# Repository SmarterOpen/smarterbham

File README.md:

# SmarterBham
The SmarterBham project
Imagine a city driven by information.  A place where decision making is supported by a city-wide sensor network that provides real time data about the state of things.  Imagine the platform that runs the network, built and owned by the citizens, measuring the things that we think are important and giving us the insights we need to make our city the best it can be. The SmarterBham project was born out of a recognition that smart cities need grassroots participation. We can combine open hardware designs with open networks, open platforms and open data policies to build a participatory smart cities future.

# Project Structure
* /lopy4 - all the code that runs on the device
* /doc - our documentation.  Requirements, wireframes, flow, security audits, etc
* /web - the web application that we use to manage devices, users, and to analyze collected data

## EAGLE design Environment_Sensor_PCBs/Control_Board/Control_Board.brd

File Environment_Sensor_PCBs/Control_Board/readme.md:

This folder will house the Control Board design filse

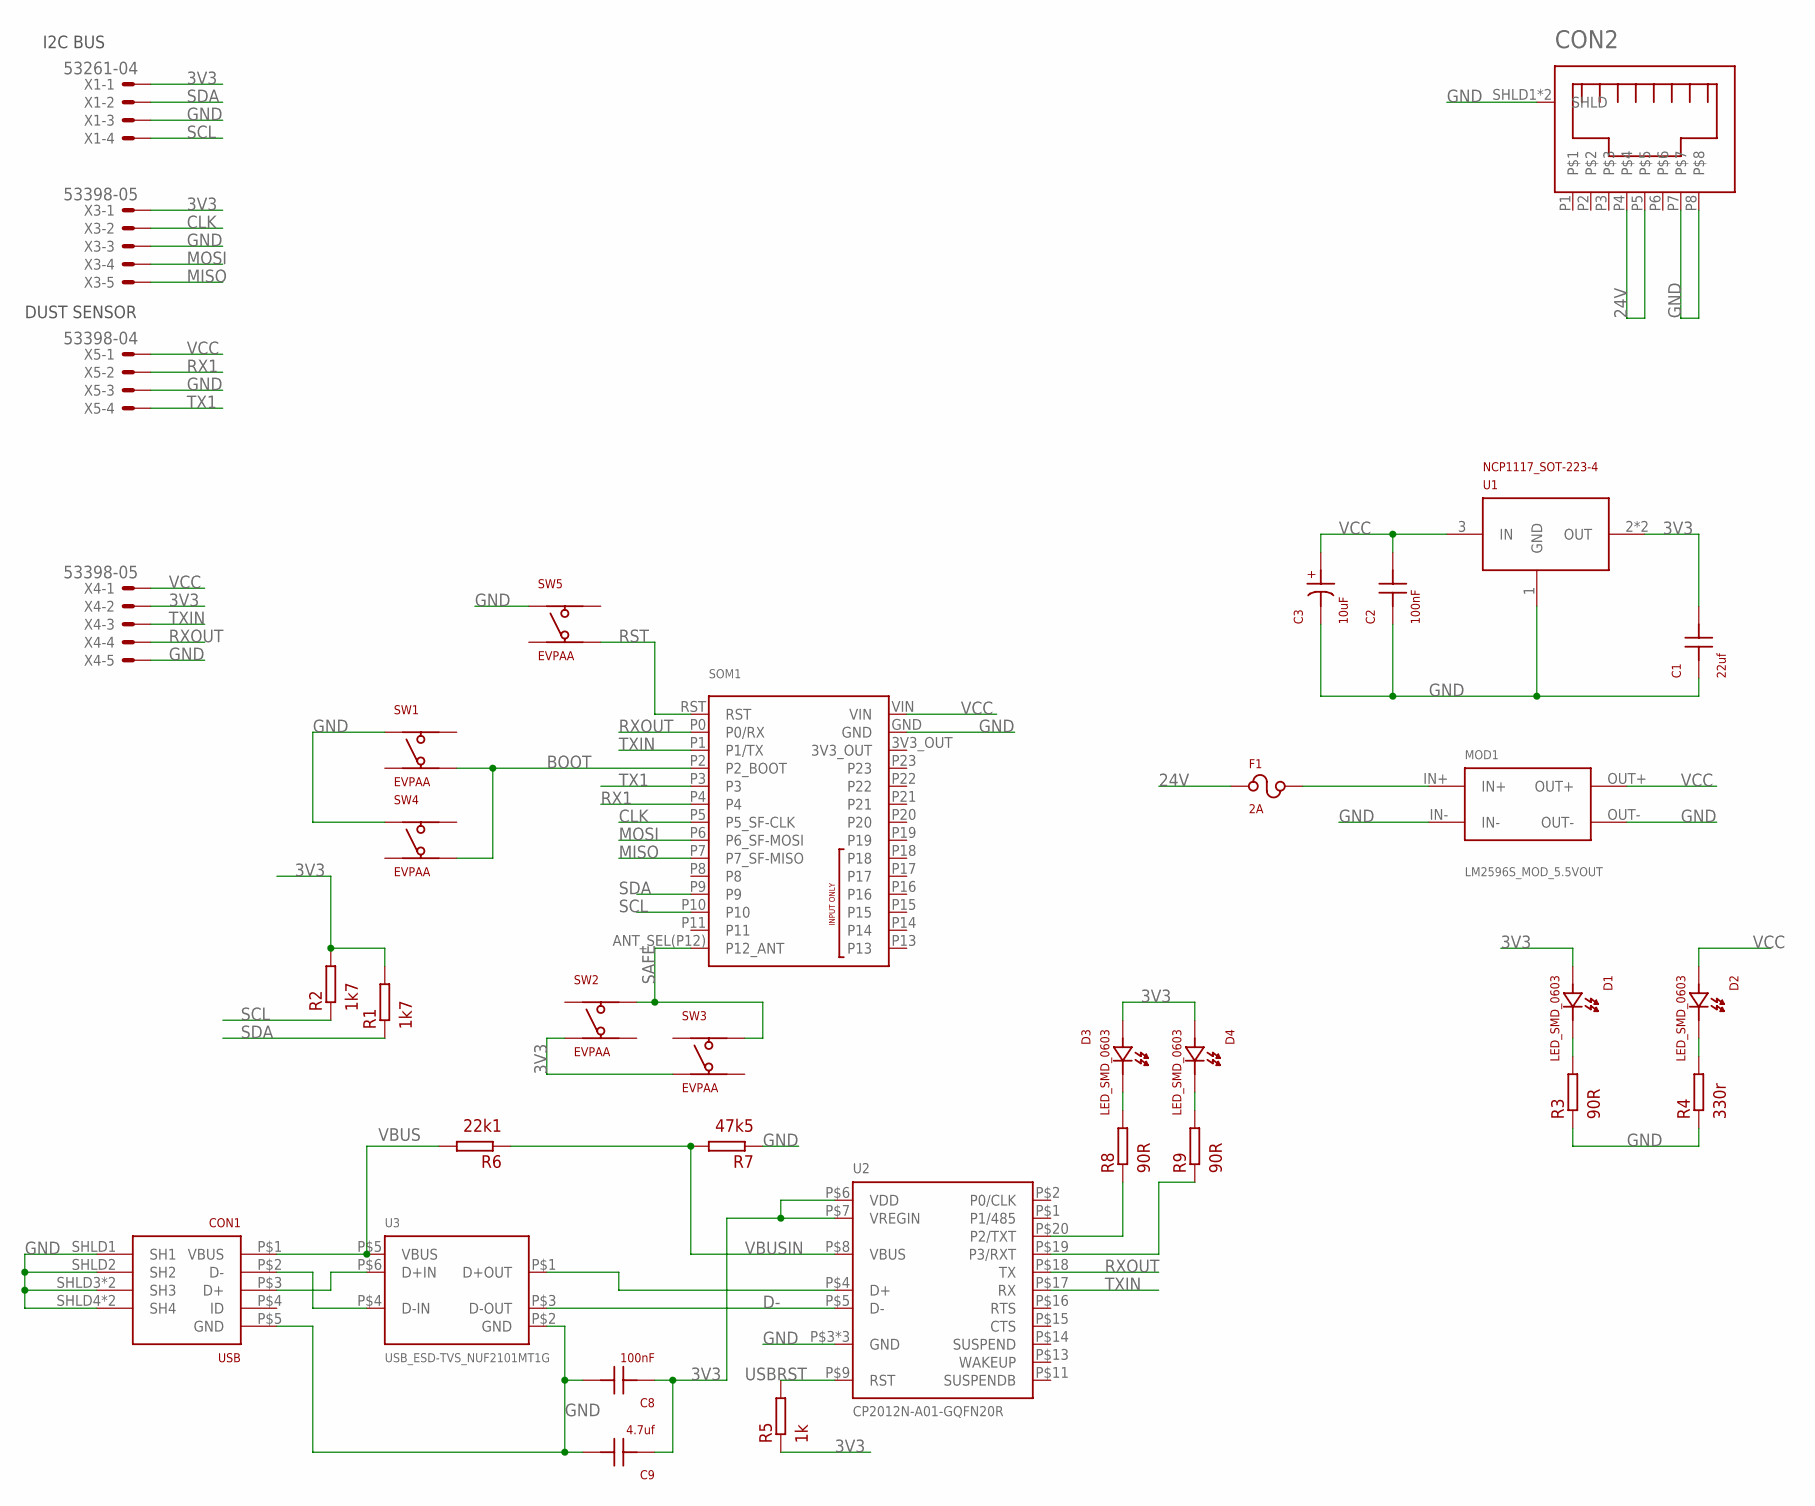
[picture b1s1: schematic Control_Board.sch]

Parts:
C1: 22uf; SMD_0603
C2, C8: 100nF; SMD_0603
C3: 10uF; CAP_POL_1206
C9: 4.7uf; SMD_0603
CON1: USB; USB_MICRO_B_SMD_AMPHENOL
CON2: P-RJLSE-4X381-01_AMPHENOL; P-RJLSE-4X381-01_AMPHENOL_SMD_RJ45
D1, D2, D3, D4: LED_SMD_0603
F1: 2A; FUSE_SMD_AUTO_MINI_LOWPROF
MOD1: LM2596S_MOD_5.5VOUT; LM2596S_MODULE
R1, R2: 1k7; SMD_0603
R3, R8, R9: 90R; SMD_0603
R4: 330r; SMD_0603
R5: 1k; SMD_0603
R6: 22k1; SMD_0603
R7: 47k5; SMD_0603
SOM1: PYCOM_LOPY4PTH; PYCOM_LOPY4_PTH
SW1, SW2, SW3, SW4, SW5: EVPAA; EVPAA_SWITCH
U1: NCP1117_SOT-223-4; SOT-223
U2: CP2012N-A01-GQFN20R; QFN20
U3: USB_ESD-TVS_NUF2101MT1G; TSOP-6
X1: 53261-04
X3, X4: 53398-05
X5: 53398-04

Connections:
3V3: C1.P$2, C8.P$1, C9.P$1, D1.A, D3.A, D4.A, R1.P$2, R2.P$2, R5.P$1, SW2.P$1 (A1), SW3.P$1 (A1), U1.2 (OUT), U1.4 (OUT), U2.P$6 (VDD), U2.P$7 (VREGIN), X1.1, X3.1, X4.2
3V3_OUT: SOM1.3V3_OUT
24V: CON2.P4, CON2.P5, F1.P1A, F1.P1B
BOOT: SOM1.P2 (P2_BOOT), SW1.P$1' (A2), SW4.P$1' (A2)
CLK: SOM1.P5 (P5_SF-CLK), X3.2
D-: U2.P$5 (D-), U3.P$3 (D-OUT)
GND: C1.P$1, C2.P$1, C3.N, C8.P$2, C9.P$2, CON1.P$5 (GND), CON1.SHLD1 (SH1), CON1.SHLD2 (SH2), CON1.SHLD3 (SH3), CON1.SHLD4 (SH4), CON1.SHLD5 (SH3), CON1.SHLD6 (SH4), CON2.P7, CON2.P8, CON2.SHLD1 (SHLD), CON2.SHLD2 (SHLD), MOD1.IN-, MOD1.OUT-, R3.P$1, R4.P$1, R7.P$1, SOM1.GND, SW1.P$2 (B1), SW4.P$2 (B1), SW5.P$2 (B1), U1.1 (GND), U2.P$3 (GND), U2.P$12 (GND), U2.PAD (GND), U3.P$2 (GND), X1.3, X3.3, X4.5, X5.3
MISO: SOM1.P7 (P7_SF-MISO), X3.5
MOSI: SOM1.P6 (P6_SF-MOSI), X3.4
unnamed: F1.P2A, F1.P2B, MOD1.IN+
unnamed: CON1.P$3 (D+), U3.P$6 (D+IN)
unnamed: U2.P$4 (D+), U3.P$1 (D+OUT)
unnamed: CON1.P$2 (D-), U3.P$4 (D-IN)
unnamed: D3.K, R8.P$2
unnamed: D4.K, R9.P$2
unnamed: R9.P$1, U2.P$19 (P3/RXT)
unnamed: R8.P$1, U2.P$20 (P2/TXT)
unnamed: D1.K, R3.P$2
unnamed: D2.K, R4.P$2
RST: SOM1.RST, SW5.P$1' (A2)
RX1: SOM1.P4, X5.2
RXOUT: SOM1.P0 (P0/RX), U2.P$18 (TX), X4.4
SAFE: SOM1.ANT_SEL(P12) (P12_ANT), SW2.P$2' (B2), SW3.P$2' (B2)
SCL: R2.P$1, SOM1.P10, X1.4
SDA: R1.P$1, SOM1.P9, X1.2
TX1: SOM1.P3, X5.4
TXIN: SOM1.P1 (P1/TX), U2.P$17 (RX), X4.3
USBRST: R5.P$2, U2.P$9 (RST)
VBUS: CON1.P$1 (VBUS), R6.P$2, U3.P$5 (VBUS)
VBUSIN: R6.P$1, R7.P$2, U2.P$8 (VBUS)
VCC: C2.P$2, C3.P, D2.A, MOD1.OUT+, SOM1.VIN, U1.3 (IN), X4.1, X5.1

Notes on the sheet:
DUST SENSOR
I2C BUS

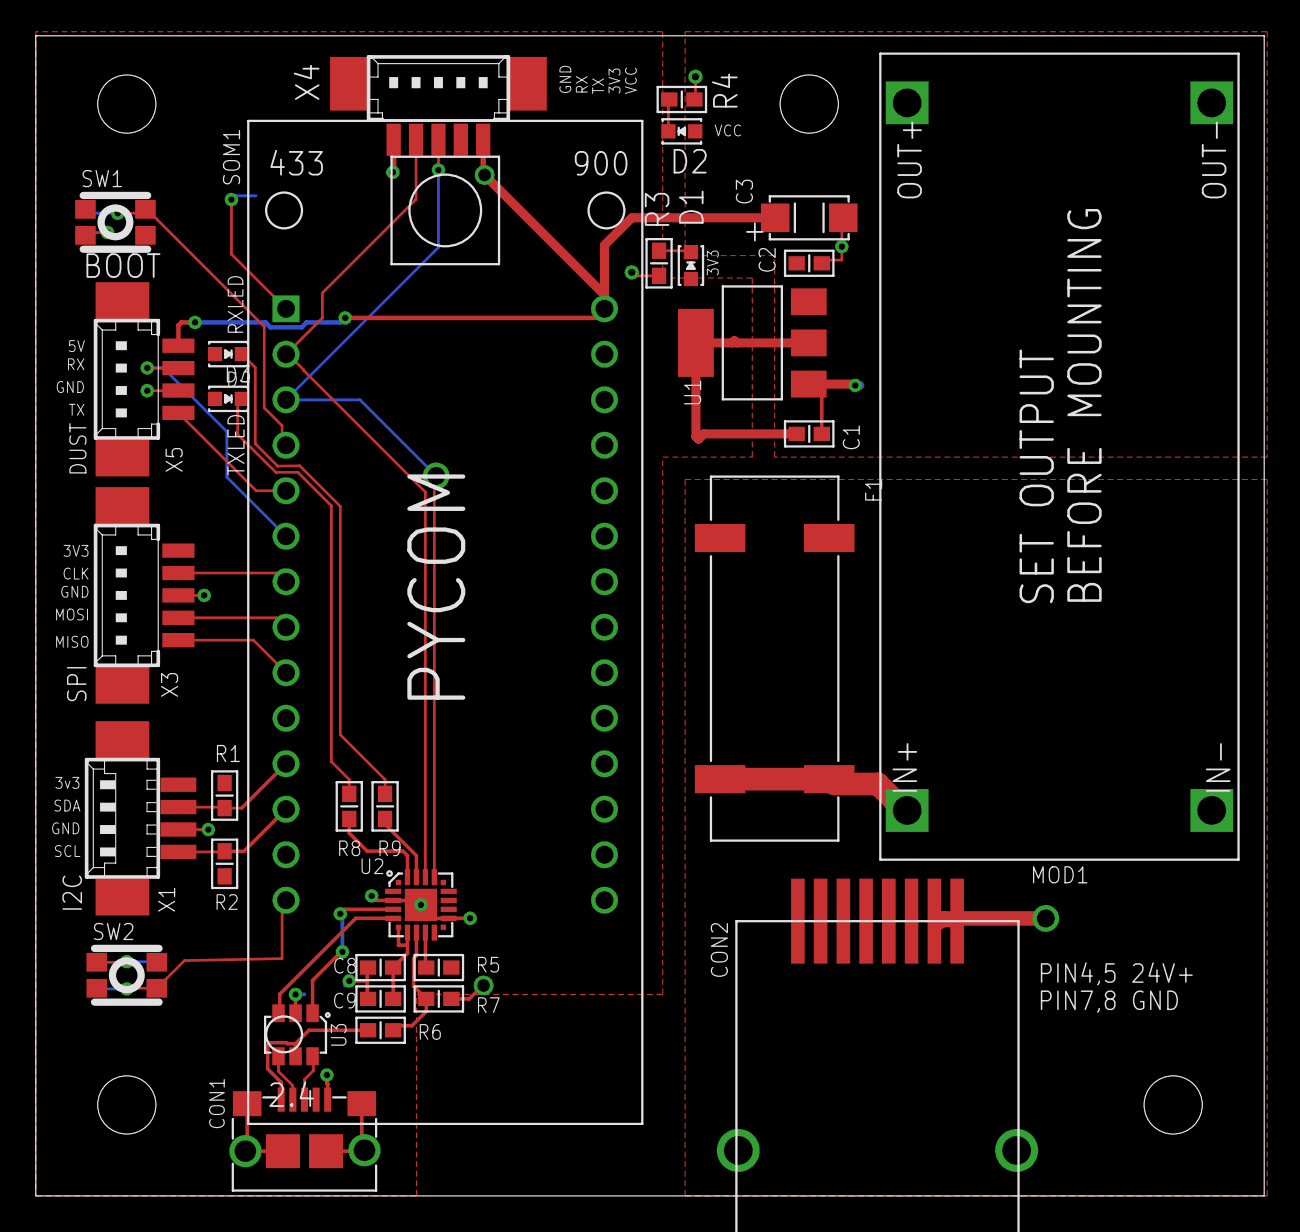
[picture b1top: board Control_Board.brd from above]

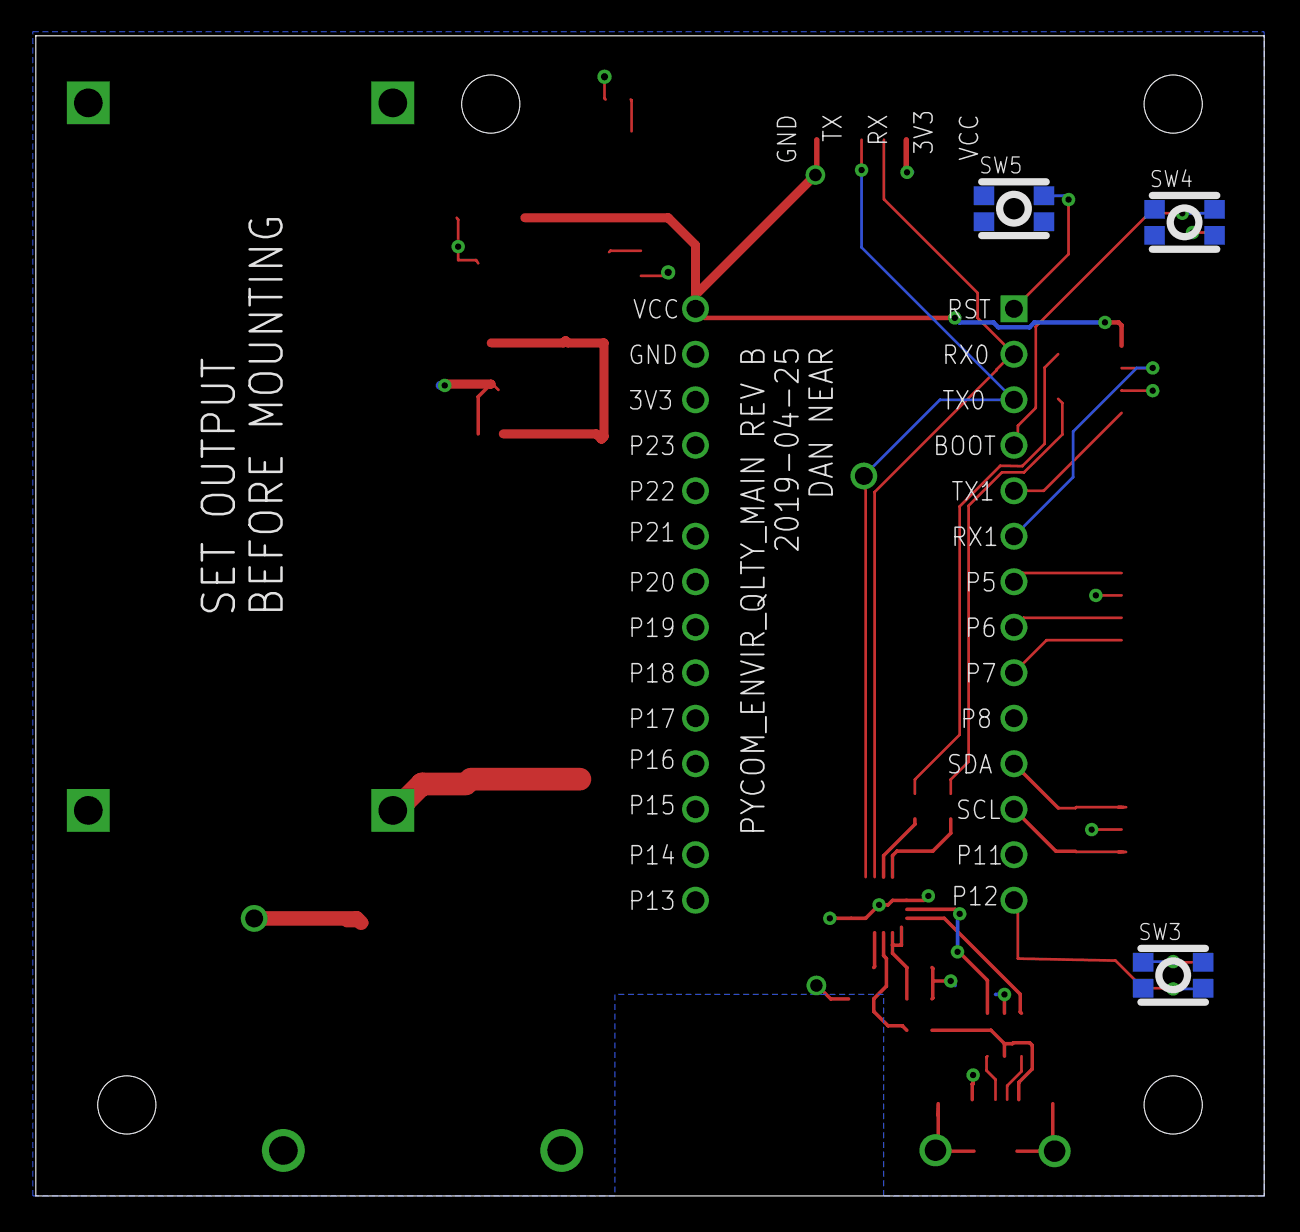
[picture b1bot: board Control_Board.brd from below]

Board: 2 copper layers, 68.6 x 64.8 mm, 35 parts (3 on the bottom side), 30 nets.

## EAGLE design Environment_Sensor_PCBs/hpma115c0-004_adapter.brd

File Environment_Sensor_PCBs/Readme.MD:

Created in Eagle 9.4
zip files contain Gerber files formatted for OSHPARK or similar.
10 unit buy has BOM from Mouser for all the parts used.  
Dust sensor was $10 cheaper each unit at newark, even after shipping.. so shop around

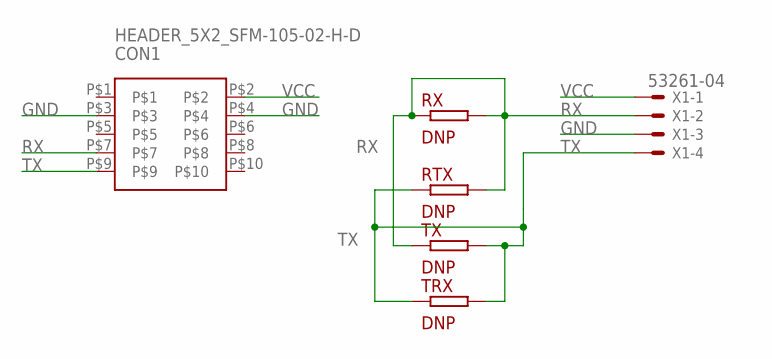
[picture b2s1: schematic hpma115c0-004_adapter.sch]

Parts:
CON1: HEADER_5X2_SFM-105-02-H-D; HEADER_5X2_1.27X1.27_SMD_SAMTEK
RTX: DNP; SMD_0402
RX: DNP; SMD_0402
TRX: DNP; SMD_0402
TX: DNP; SMD_0402
X1: 53261-04

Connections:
GND: CON1.P$3, CON1.P$4, X1.3
RX: CON1.P$7, RTX.P$2, RX.P$1, RX.P$2, TX.P$1, X1.2
TX: CON1.P$9, RTX.P$1, TRX.P$1, TRX.P$2, TX.P$2, X1.4
VCC: CON1.P$2, X1.1

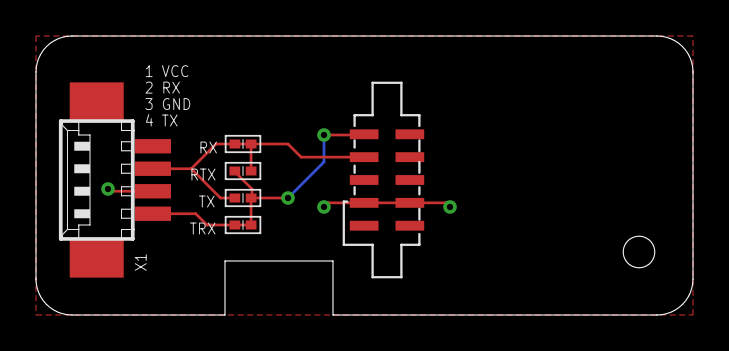
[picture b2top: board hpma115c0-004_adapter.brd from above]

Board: 2 copper layers, 36.5 x 15.5 mm, 6 parts (0 on the bottom side), 4 nets.

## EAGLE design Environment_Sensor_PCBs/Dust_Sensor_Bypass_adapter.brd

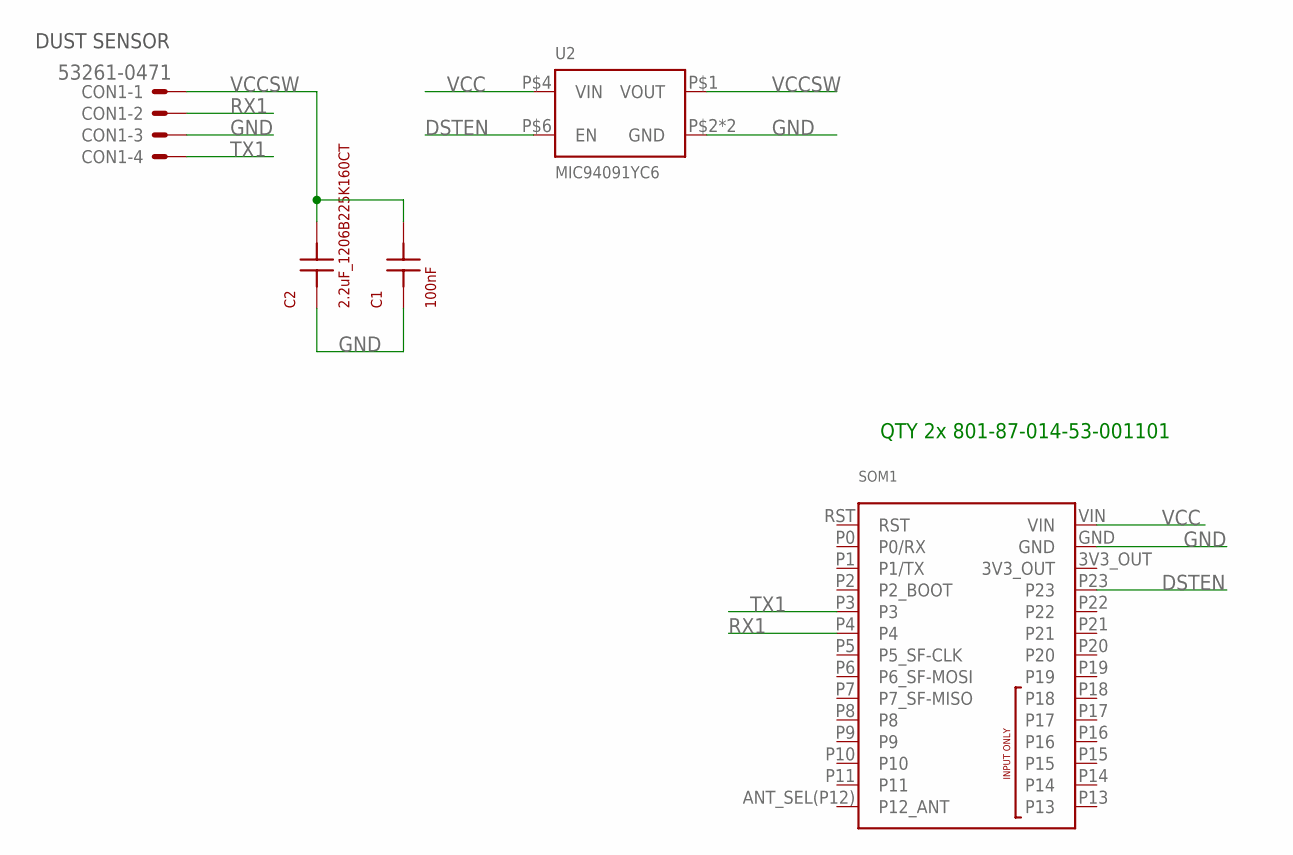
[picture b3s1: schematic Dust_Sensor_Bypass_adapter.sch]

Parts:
C1: 100nF; SMD_0603
C2: 2.2uF_1206B225K160CT; SMD_1206
CON1: 53261-0471; 53261-04
SOM1: PYCOM_LOPY4PTH; PYCOM_LOPY4_PTH
U2: MIC94091YC6; SC-70(C6)

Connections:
3V3_OUT: SOM1.3V3_OUT
DSTEN: SOM1.P23, U2.P$6 (EN)
GND: C1.P$1, C2.P$1, CON1.3, SOM1.GND, U2.P$2 (GND), U2.P$5 (GND)
RX1: CON1.2, SOM1.P4
TX1: CON1.4, SOM1.P3
VCC: SOM1.VIN, U2.P$4 (VIN)
VCCSW: C1.P$2, C2.P$2, CON1.1, U2.P$1 (VOUT)

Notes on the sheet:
DUST SENSOR
QTY 2x 801-87-014-53-001101

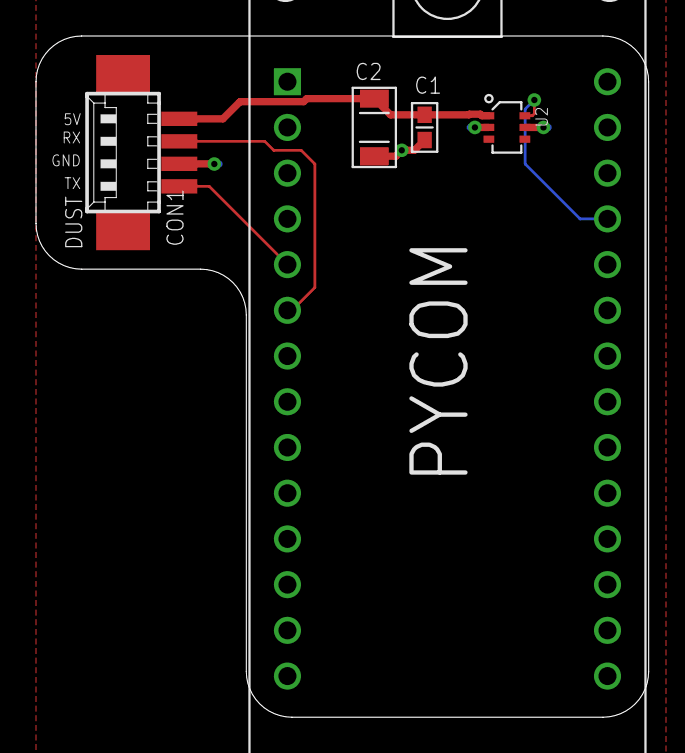
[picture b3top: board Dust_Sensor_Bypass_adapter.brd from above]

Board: 2 copper layers, 34.0 x 37.8 mm, 5 parts (0 on the bottom side), 6 nets.

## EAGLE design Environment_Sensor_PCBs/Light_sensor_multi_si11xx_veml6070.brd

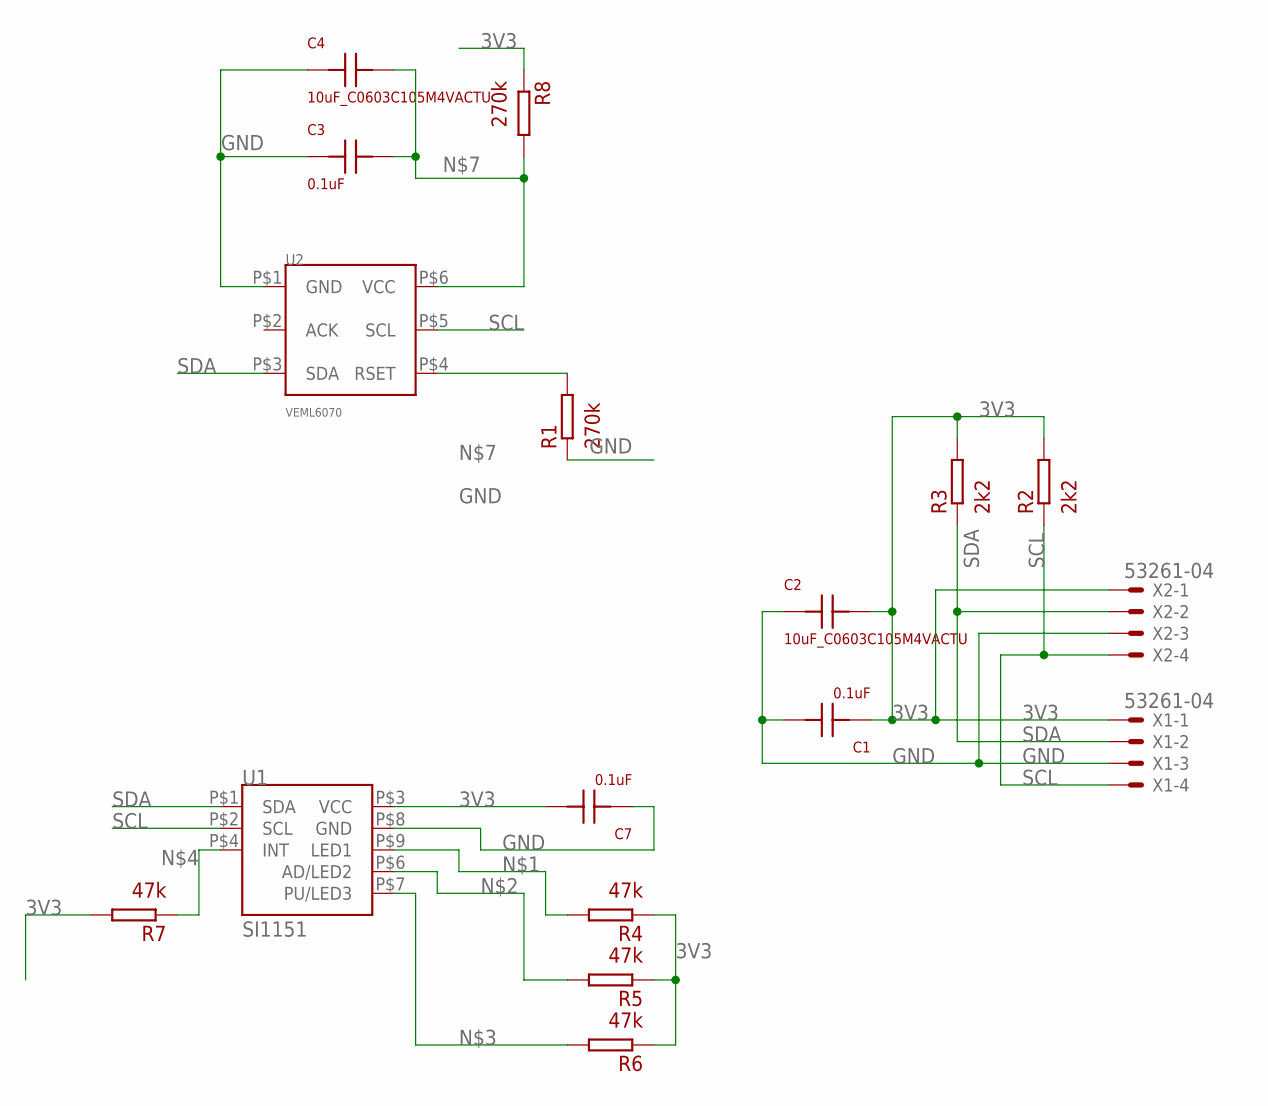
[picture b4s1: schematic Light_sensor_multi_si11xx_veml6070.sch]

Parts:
C1, C3, C7: 0.1uF; SMD_0402
C2, C4: 10uF_C0603C105M4VACTU; SMD_1206
R1, R8: 270k; SMD_0402
R2, R3: 2k2; SMD_0402
R4, R5, R6, R7: 47k; SMD_0402
U1: SI1151; QFN10
U2: VEML6070; OPLGA-6
X1, X2: 53261-04

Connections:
3V3: C1.P$1, C2.P$2, C7.P$2, R2.P$2, R3.P$2, R4.P$1, R5.P$1, R6.P$1, R7.P$2, R8.P$1, U1.P$3 (VCC), X1.1, X2.1
GND: C1.P$2, C2.P$1, C3.P$1, C4.P$1, C7.P$1, R1.P$1, U1.P$8 (GND), U2.P$1 (GND), X1.3, X2.3
unnamed: R4.P$2, U1.P$9 (LED1)
unnamed: R5.P$2, U1.P$6 (AD/LED2)
unnamed: R6.P$2, U1.P$7 (PU/LED3)
unnamed: R7.P$1, U1.P$4 (INT)
unnamed: R1.P$2, U2.P$4 (RSET)
unnamed: C3.P$2, C4.P$2, R8.P$2, U2.P$6 (VCC)
SCL: R2.P$1, U1.P$2 (SCL), U2.P$5 (SCL), X1.4, X2.4
SDA: R3.P$1, U1.P$1 (SDA), U2.P$3 (SDA), X1.2, X2.2

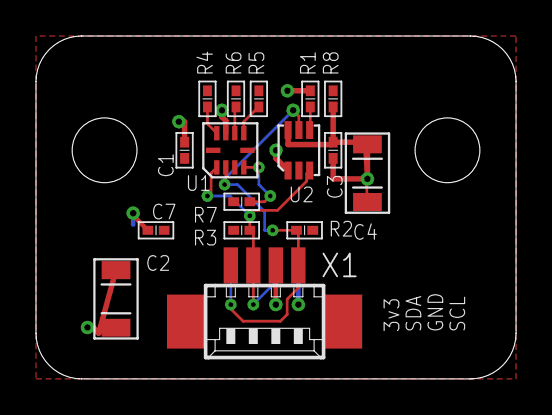
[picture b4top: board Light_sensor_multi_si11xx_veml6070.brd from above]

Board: 2 copper layers, 26.7 x 19.1 mm, 17 parts (1 on the bottom side), 10 nets.

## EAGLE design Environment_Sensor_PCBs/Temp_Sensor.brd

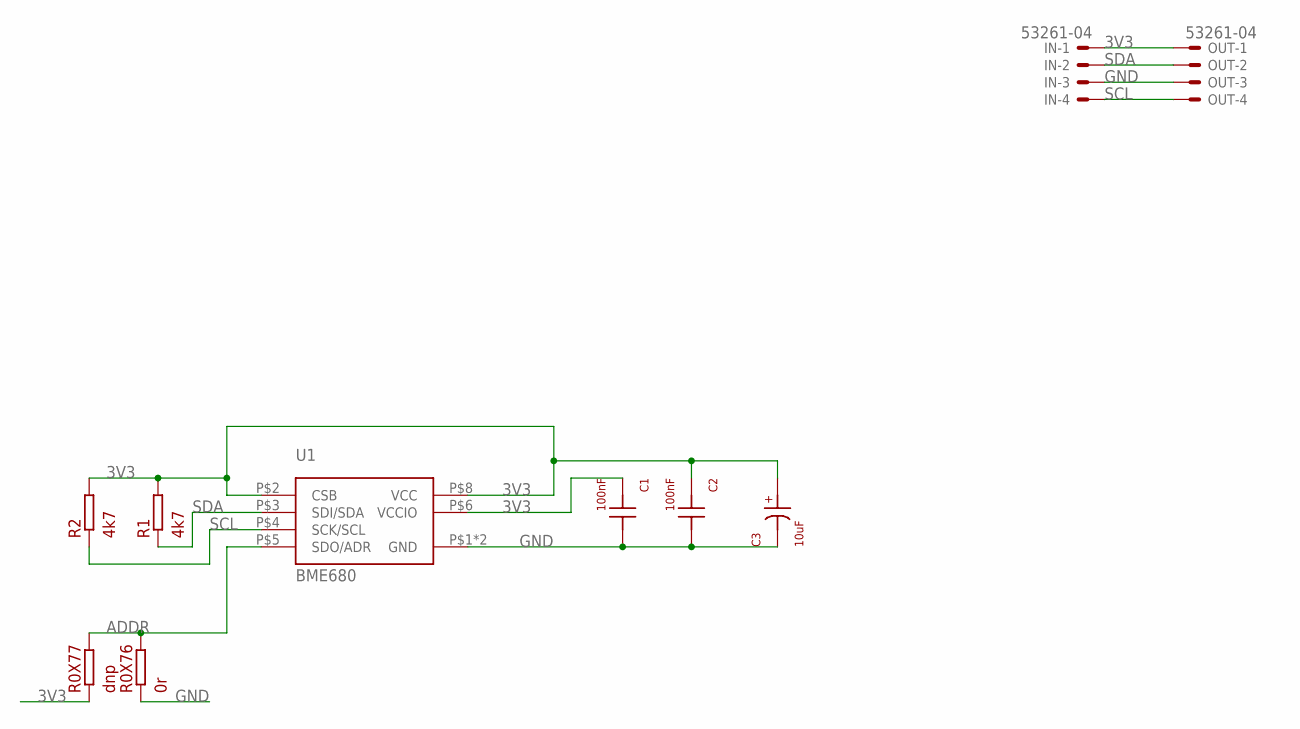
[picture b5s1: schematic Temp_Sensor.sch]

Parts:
C1, C2: 100nF; SMD_0402
C3: 10uF; CAP_POL_1206
IN: 53261-04
OUT: 53261-04
R0X76: 0r; SMD_0402
R0X77: dnp; SMD_0402
R1, R2: 4k7; SMD_0402
U1: BME680; BOSCH_LGA8

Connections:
3V3: C1.P$1, C2.P$1, C3.P, IN.1, OUT.1, R0X77.P$1, R1.P$2, R2.P$2, U1.P$2 (CSB), U1.P$6 (VCCIO), U1.P$8 (VCC)
ADDR: R0X76.P$2, R0X77.P$2, U1.P$5 (SDO/ADR)
GND: C1.P$2, C2.P$2, C3.N, IN.3, OUT.3, R0X76.P$1, U1.P$1 (GND), U1.P$7 (GND)
SCL: IN.4, OUT.4, R2.P$1, U1.P$4 (SCK/SCL)
SDA: IN.2, OUT.2, R1.P$1, U1.P$3 (SDI/SDA)

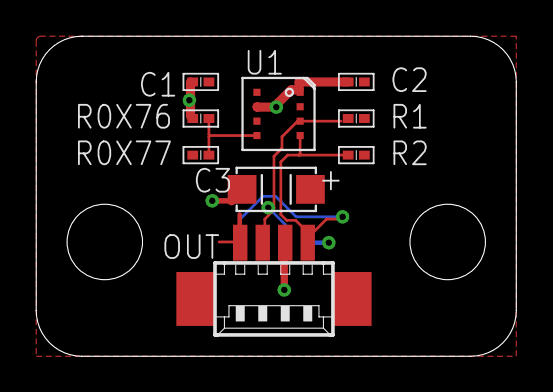
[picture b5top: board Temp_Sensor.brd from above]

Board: 2 copper layers, 26.7 x 17.8 mm, 10 parts (1 on the bottom side), 5 nets.

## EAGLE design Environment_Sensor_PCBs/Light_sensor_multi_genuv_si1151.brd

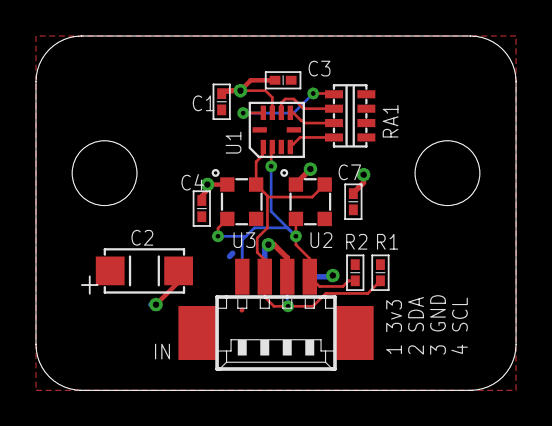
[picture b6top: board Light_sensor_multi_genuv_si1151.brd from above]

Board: 2 copper layers, 26.7 x 19.7 mm, 13 parts (1 on the bottom side), 8 nets.

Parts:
C1, C3, C4, C7: 0.1uF; SMD_0402
C2: 10uF; CAP_POL_1206
IN: 53261-04
OUT: 53261-04
R1, R2: 1k8; SMD_0402
RA1: 47k; SMD_4X_0603
U1: SI115X_I2C_LIGHT_SENSOR_PROX_GM; QFN10
U2: GUVA_C32SM; 2X2.3OLGA
U3: GUVb_C31SM; 2X2.3OLGA

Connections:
3V3: C1.P$1, C2.P, C3.P$2, C4.P$2, C7.P$2, IN.1, OUT.1, R1.P$2, R2.P$2, RA1.5, RA1.6, RA1.7, RA1.8, U1.P$3, U2.P$4, U3.P$4
GND: C1.P$2, C2.N, C3.P$1, C4.P$1, C7.P$1, IN.3, OUT.3, U1.P$8, U2.P$1, U3.P$1
unnamed: RA1.1, U1.P$9
unnamed: RA1.3, U1.P$6
unnamed: RA1.2, U1.P$7
unnamed: RA1.4, U1.P$4
SCL: IN.4, OUT.4, R2.P$1, U1.P$2, U2.P$3, U3.P$3
SDA: IN.2, OUT.2, R1.P$1, U1.P$1, U2.P$2, U3.P$2

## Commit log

2019-06-16 Current release of boards
    These are the boards files used in the initial 1o sensor prototypes, plus the full BOM
2019-06-16 Uploaded schematic files for existing builds
2019-06-25 initial firmware to read HPMA115S0 dust sensor - nonfunctional as of yet
2019-06-25 Update abpkeys.py
    Added note to keys file
2019-06-25 Update main.py
    Added comments
2019-06-25 Update hpma115s0.py
    Added comments
2019-06-25 Update lora.py
    Added the existing code running from main.py on Pycom_Dust_06
    This is just outputting static values and needs to be rewritten as a library to make it easier to read
    but I dumped the data here to aid in that.
2019-06-25 Create readme.MD
    Deprecating this branch since we abandoned the Raspi Zero W project
2019-06-25 Create bme680.py
    Created library place holder for BME680 sensor code
2019-06-25 Create veml6070.py
    Library placeholder for Vishay VEML6070 code
2019-06-25 Create si11xx.py
    Created library placeholder for si1132 and si1151 digital ambient light sensors
2019-06-25 Update bme680.py
    Link to Adafruit Micropython code sample for the BME680
2019-06-26 Update si11xx.py
    Adding sample code from Silabs AN498 Application Note
2019-06-26 Update si11xx.py
    Added more code snippets from SiLabs AN498
2019-06-26 Update si11xx.py
    Added code from a Python source project - needs conversion to Micropython
2019-06-26 Update bme680.py
    INput code from someone elses pycom project
2019-06-26 Create constants.py
    Code from another BME680 pycom project
2019-06-26 Create i2c.py
    Copied code from another Pycom project
2019-06-26 Update main.py
    BME680 code from Wipy project.. needs testing.. may be functional
2019-06-28 Update bme680.py
    smbus declaration was for RasPi python.. changed to Pycom-standard i2c initialization
2019-06-28 Update main.py
    BME680 code tested, just needs some small tweaks to feed data to Lora.
2019-06-28 Update bme680.py
    Code tested
2019-07-04 Update main.py
    Added working LoRa OTAA code
2019-07-04 Update abpkeys.py
    Added OTAA key parameters with blanked out values
2019-07-05 Update bme680.py
    Added DewPoint Calculation
2019-07-06 Update main.py
    changed abpkeys.py to lorakeys.py
2019-07-06 Update main.py
    Adding VOC data to the output - but haven't figured out how to send the Long value
2019-07-06 Update hpma115s0.py
    Debugged code in readbytes and readstringuntil. these are closer to operational now but the routine calling them still fails to detect correct sequence
2019-10-21 Test sample code for HPMA sensor
    Testing with start/stop functionality for sensor longevity
    Output:
    waking up HPMA
    b'\xa5\xa5'
    disable Autosend
    b'\xa5\xa5'
2019-10-21 Rename HPMA_Sample_code to HPMA_Sample_code.py
2019-12-18 Current 3d printed housing design
    These parts are printed using white PETG, 0.4mm nozzle and .3mm layer height, upside down with no supports.
2020-03-13 Adding code to talk to the si1132 sensor
    Some of the boards have si1132 IR/Ambient sensors, this code will talk with them.
2020-03-13 Added module to talk to the si1132 sensor
    This module communicates with the sensor, and only a few code additions needed in main.py to connect
2020-06-10 Created a patch to control dust sensor power
    This adapter board fits between the main board and the Pycom module, and allows you to power cycle the dust sensor by turning p23 high(On) or low(Off). It helps since the Honeywell HPMA115S0 dust sen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
2020-08-06 Update main.py
    Added some code to detect when I2C sensors were connected and skip over code that referred to disconnected sensors. It's not perfect yet but seems to allow the same code to work in a few places.
2020-10-16 Update main.py
    Merged the code I had working on new and old sensor platforms to support both from the same base code.
2020-10-18 Update main.py
    Verified and added the address for the si1151 parts that have the wrong i2c address burned in from the factory
2020-10-18 Update main.py
    Changed default values for particulate to 0 instead of -1
2020-10-20 Update main.py
    VOCStruct initialized as Int instead of Long - causes crash when BME680 not reporting properly.
2020-10-26 Update README.md
    Switched devices to Pycom LoPy4
2020-11-04 Adding battery measurement capability
    Added a voltage divider to P13 to measure input voltage, so we can remotely monitor/diagnose solar charging status. Devices that don't have the divider will simply read 0v and can be retrofitted with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
2020-11-05 Update main.py
    Added ADC initialization for battery voltage
2020-11-12 Adding most recent boards
2020-11-12 Creating separate folders for each PCB
    This folder will house the Control Board design filse
2020-11-12 Rename Environment_Sensor_PCBs/Control_Board.brd to Environment_Sensor_PCBs/Control_Board/Control_Board.brd
    Moving to a separate folder
2020-11-12 Rename Environment_Sensor_PCBs/Control_Board.sch to Environment_Sensor_PCBs/Control_Board/Control_Board.sch
2020-11-18 Update main.py
    Improved boot process by properly restoring LoRa nvram before join process. If it's already joined, it can skip the join process, wasting less time before beginning measurements
2020-11-25 Update main.py
    Revised battery voltage calculation
2020-11-27 Update main.py
    added more debug notes to trace down failures, sped up wifi connection when primary AP already connected on start
2021-03-03 Create boot.py
    Adding Bluetooth deinit process to reduce power consumption some
2021-06-10 Update boot.py
    Had to properly initialize Bluetooth to deinit it.
